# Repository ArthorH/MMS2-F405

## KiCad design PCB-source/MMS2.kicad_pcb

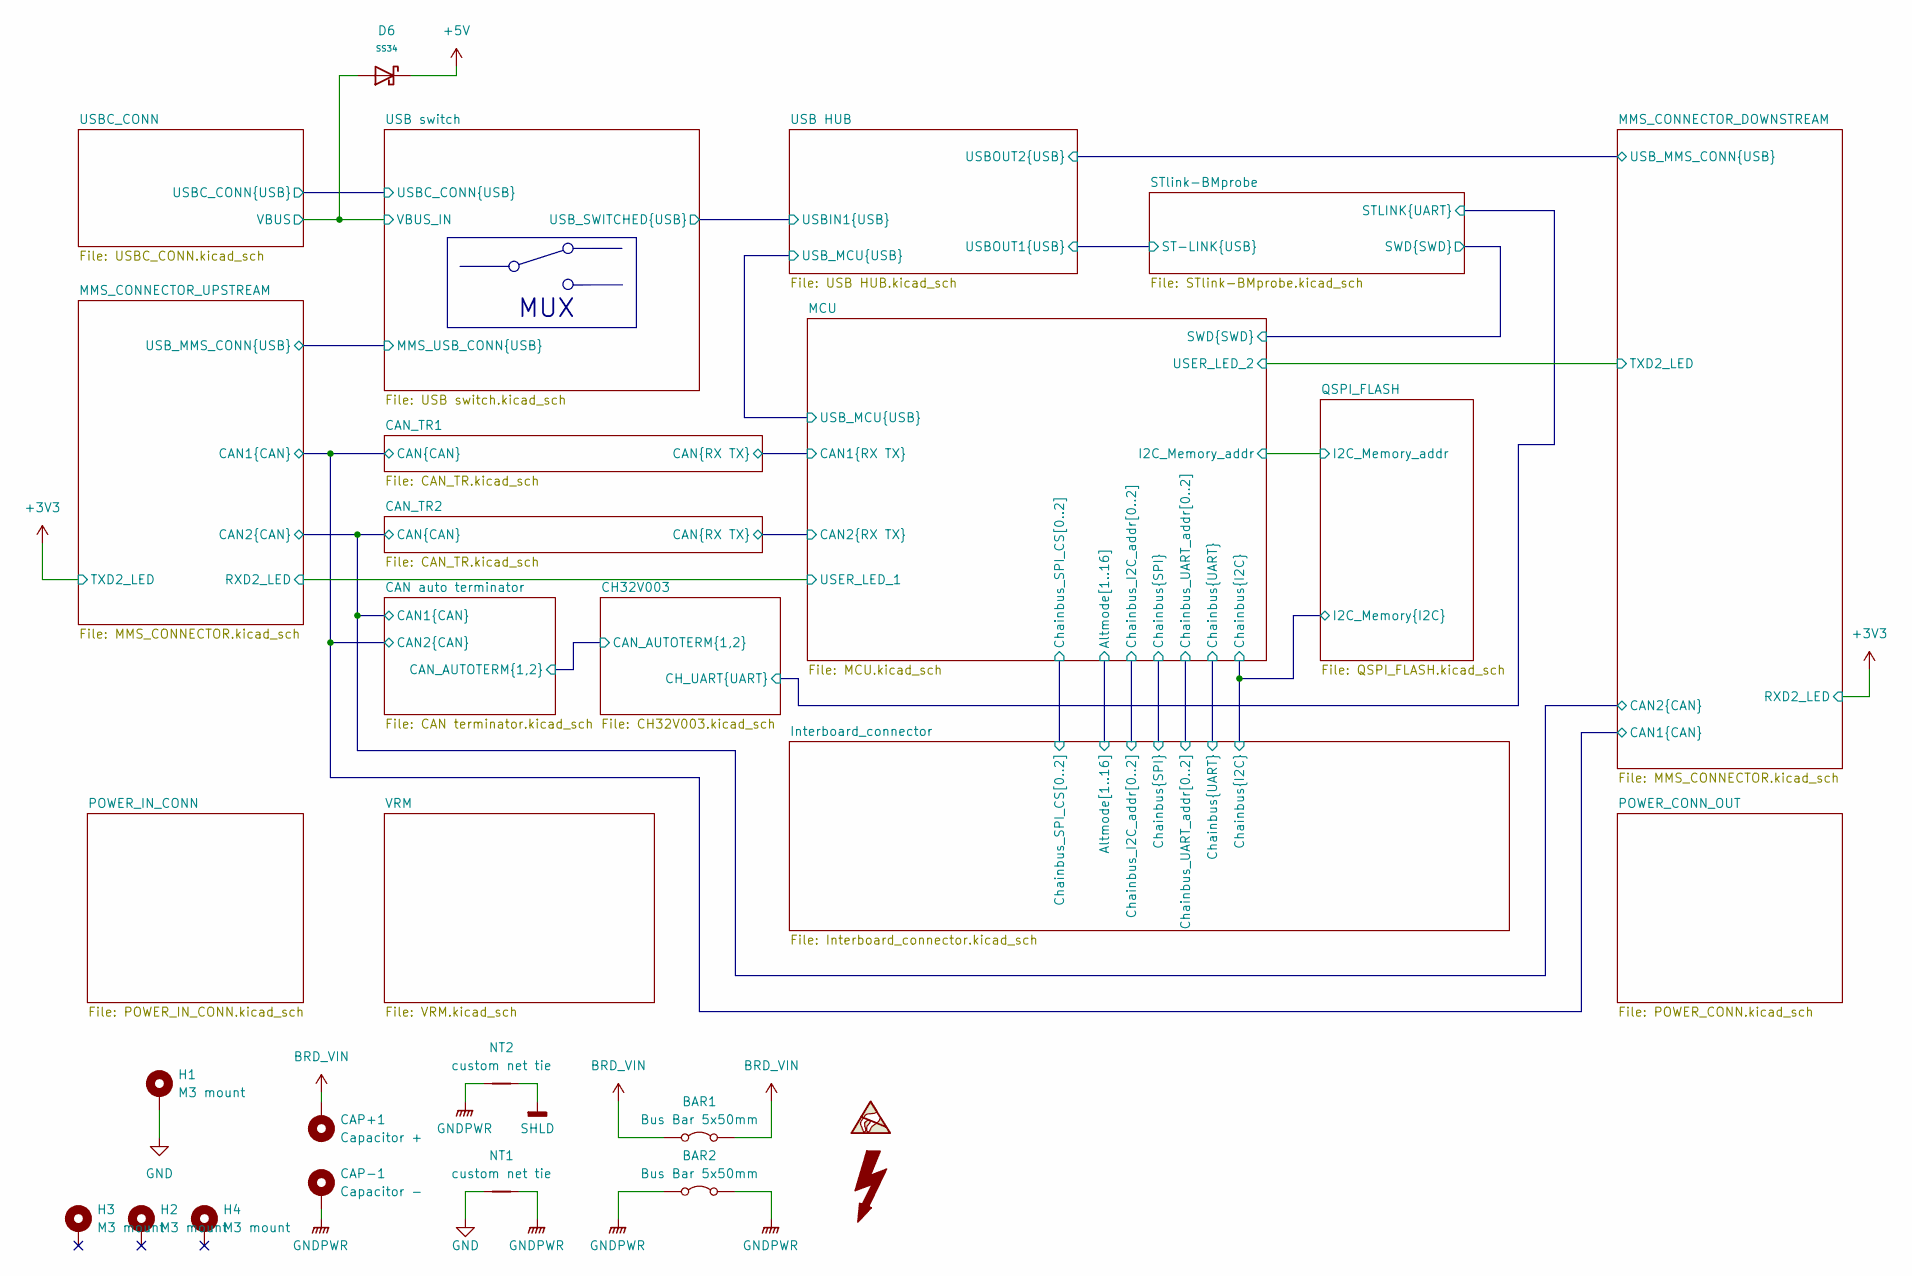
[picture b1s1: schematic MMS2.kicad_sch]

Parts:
BAR1: Bus Bar 5x50mm; BusBar-50mm-Red
BAR2: Bus Bar 5x50mm; BusBar-50mm-black
CAP+1: Capacitor +; TestPoint_THTPad_1.5x1.5mm_Drill0.7mm
CAP-1: Capacitor -; TestPoint_THTPad_1.5x1.5mm_Drill0.7mm
D6: SS34; D_SMA; Forward Voltage (Vf@If) 550mV@3A; Reverse Voltage (Vr) 40V; Part SS34; LCSC C8678
H1, H2: M3 mount; MountingHole_3.2mm_M3_DIN965_Pad
H3, H4: M3 mount; MountingHole_3.2mm_M3_DIN965_Pad; LCSC C49236535
NT1: custom net tie; Custom
NT2: custom net tie; SHLD

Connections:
+5V: D6.1; also elsewhere on the board
BRD_VIN: BAR1.1 (A), BAR1.2 (B), CAP+1.1; also elsewhere on the board
GND: H1.1, NT1.1; also elsewhere on the board
GNDPWR: BAR2.1 (A), BAR2.2 (B), CAP-1.1, NT1.2, NT2.1; also elsewhere on the board
SHLD: NT2.2
VBUS: D6.2; also elsewhere on the board

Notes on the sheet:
MUX

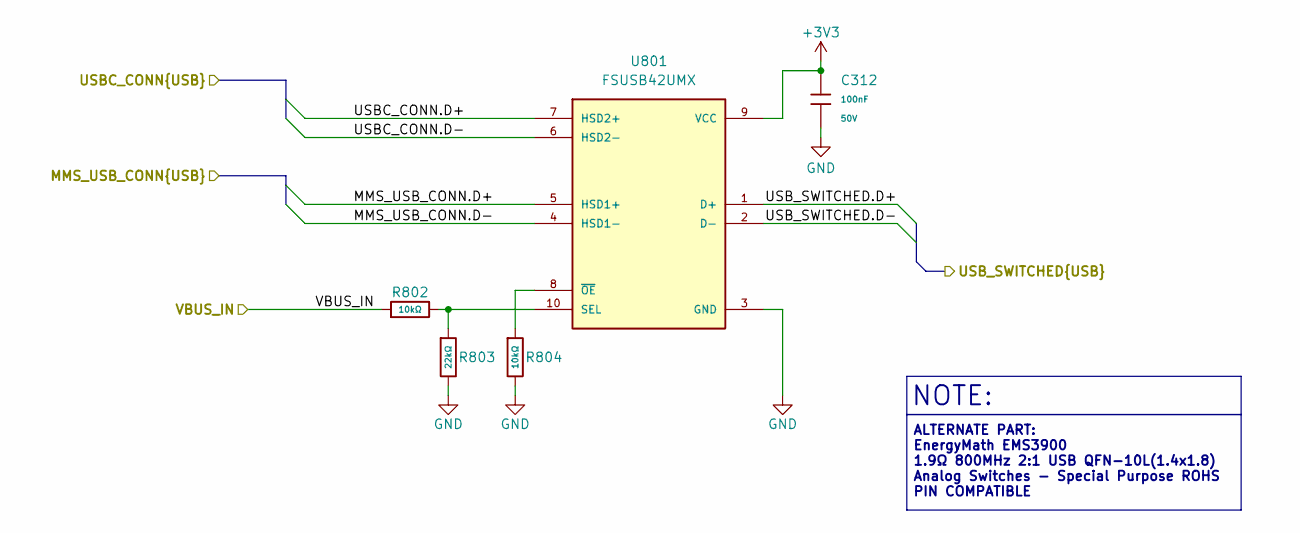
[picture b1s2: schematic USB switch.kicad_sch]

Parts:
C312: 100nF; C_0402; Voltage Rated 50V; Tolerance ±10%; Part CL05B104KB54PNC; LCSC C307331
R802, R804: 10kΩ; R_0402; Overload Voltage (Max) 50V; Tolerance ±1%; Part 0402WGF1002TCE; LCSC C25744
R803: 22kΩ; R_0402; Overload Voltage (Max) 50V; Tolerance ±1%; Part 0402WGF2202TCE; LCSC C25768
U801: FSUSB42UMX; UFQFN-10_1.4x1.8; PARTREV 1.25; LCSC C11145

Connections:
+3V3: C312.1, U801.9 (VCC); also elsewhere on the board
/MMS_CONNECTOR_UPSTREAM/USB_MMS_CONN.D+: U801.5 (HSD1+); also elsewhere on the board
/MMS_CONNECTOR_UPSTREAM/USB_MMS_CONN.D-: U801.4 (HSD1-); also elsewhere on the board
/USB HUB/USBIN1.D+: U801.1 (D+); also elsewhere on the board
/USB HUB/USBIN1.D-: U801.2 (D-); also elsewhere on the board
/USB switch/USBC_CONN.D+: U801.7 (HSD2+); also elsewhere on the board
/USB switch/USBC_CONN.D-: U801.6 (HSD2-); also elsewhere on the board
GND: C312.2, R803.2, R804.2, U801.3 (GND); also elsewhere on the board
unnamed: R802.2, R803.1, U801.10 (SEL)
unnamed: R804.1, U801.8 (~OE)
VBUS: R802.1; also elsewhere on the board

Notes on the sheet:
NOTE:
ALTERNATE PART: EnergyMath EMS3900 1.9Ω 800MHz 2:1 USB QFN-10L(1.4x1.8) Analog Switches - Special Purpose ROHS PIN COMPATIBLE

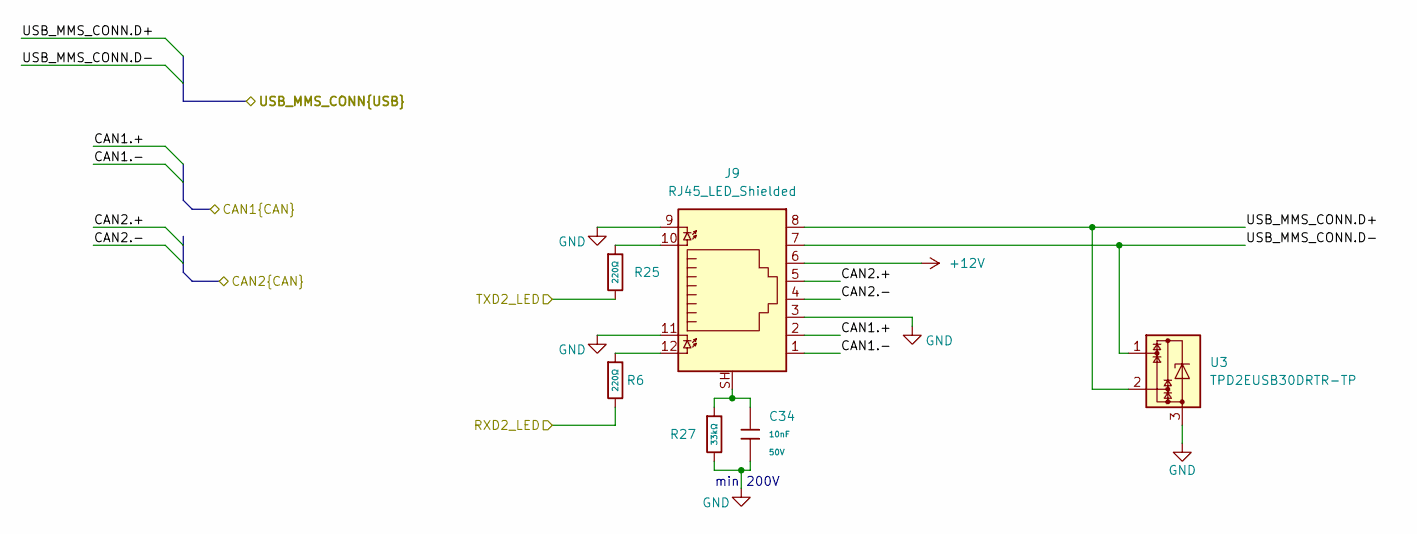
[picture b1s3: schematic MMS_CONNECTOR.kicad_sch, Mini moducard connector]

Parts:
C34: 10nF; C_0402; Voltage Rated 50V; Tolerance ±10%; Part CL05B103KB5NNNC; LCSC C15195
J9: RJ45_LED_Shielded; RJ45_Amphenol_RJHSE538X
R6, R25: 220Ω; R_0402; Overload Voltage (Max) 50V; Tolerance ±1%; Part 0402WGF2200TCE; LCSC C25091
R27: 33kΩ; R_0402; Overload Voltage (Max) 50V; Tolerance ±1%; Part 0402WGF3302TCE; LCSC C25779
U3: TPD2EUSB30DRTR-TP; SOT-723; LCSC C2844720

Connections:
+3V3: R6.2; also elsewhere on the board
+12V: J9.6; also elsewhere on the board
/CAN auto terminator/CAN1.+: J9.5; also elsewhere on the board
/CAN auto terminator/CAN1.-: J9.4; also elsewhere on the board
/CAN auto terminator/CAN2.+: J9.2; also elsewhere on the board
/CAN auto terminator/CAN2.-: J9.1; also elsewhere on the board
/MCU/USER_LED_2: R25.2; also elsewhere on the board
/MMS_CONNECTOR_DOWNSTREAM/USB_MMS_CONN.D+: J9.8, U3.2; also elsewhere on the board
/MMS_CONNECTOR_DOWNSTREAM/USB_MMS_CONN.D-: J9.7, U3.1; also elsewhere on the board
GND: C34.2, J9.3, J9.9, J9.11, R27.2, U3.3; also elsewhere on the board
unnamed: C34.1, J9.SH, R27.1
unnamed: J9.10, R25.1
unnamed: J9.12, R6.1

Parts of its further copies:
C45: 10nF; C_0402; Voltage Rated 50V; Tolerance ±10%; Part CL05B103KB5NNNC; LCSC C15195
J8: RJ45_LED_Shielded; RJ45_Amphenol_RJHSE538X
R26, R53: 220Ω; R_0402; Overload Voltage (Max) 50V; Tolerance ±1%; Part 0402WGF2200TCE; LCSC C25091
R51: 33kΩ; R_0402; Overload Voltage (Max) 50V; Tolerance ±1%; Part 0402WGF3302TCE; LCSC C25779
U4: TPD2EUSB30DRTR-TP; SOT-723; LCSC C2844720

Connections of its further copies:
+3V3: R26.2; also elsewhere on the board
+12V: J8.6; also elsewhere on the board
/CAN auto terminator/CAN1.+: J8.5; also elsewhere on the board
/CAN auto terminator/CAN1.-: J8.4; also elsewhere on the board
/CAN auto terminator/CAN2.+: J8.2; also elsewhere on the board
/CAN auto terminator/CAN2.-: J8.1; also elsewhere on the board
/MCU/USER_LED_1: R53.2; also elsewhere on the board
/MMS_CONNECTOR_UPSTREAM/USB_MMS_CONN.D+: J8.8, U4.2; also elsewhere on the board
/MMS_CONNECTOR_UPSTREAM/USB_MMS_CONN.D-: J8.7, U4.1; also elsewhere on the board
GND: C45.2, J8.3, J8.9, J8.11, R51.2, U4.3; also elsewhere on the board
unnamed: C45.1, J8.SH, R51.1
unnamed: J8.10, R26.1
unnamed: J8.12, R53.1

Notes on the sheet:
min 200V

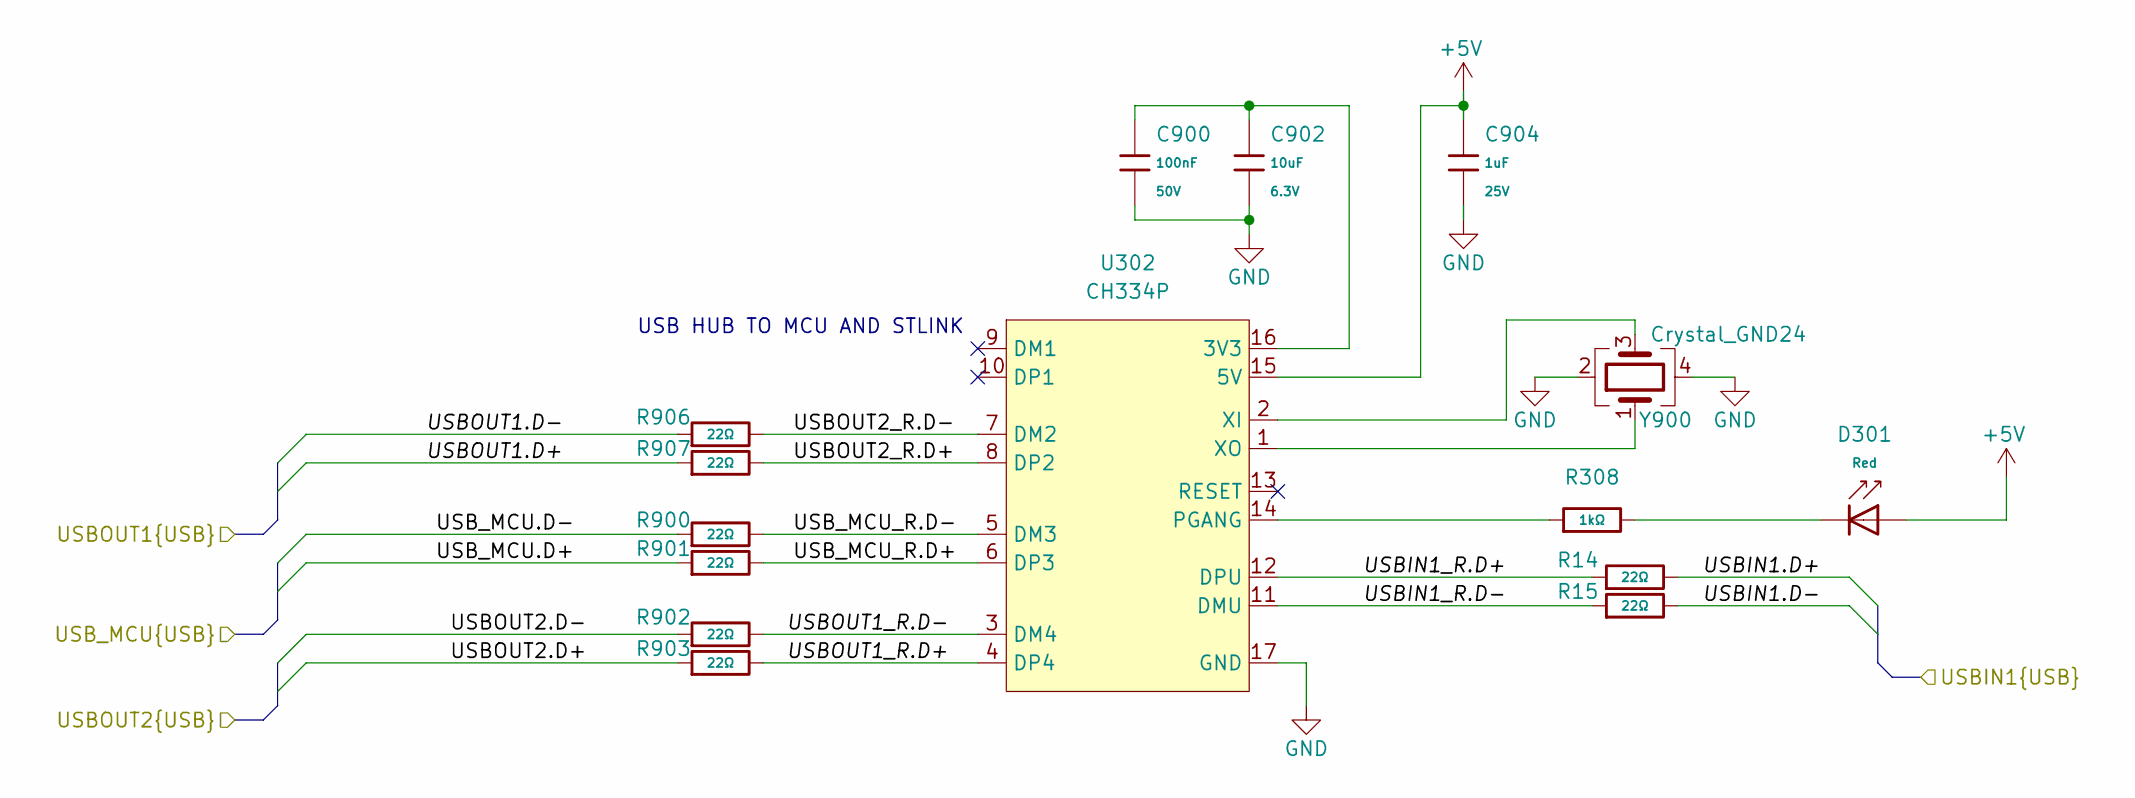
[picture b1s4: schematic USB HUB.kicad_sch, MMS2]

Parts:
C900: 100nF; C_0402; Voltage Rated 50V; Tolerance ±10%; Part CL05B104KB54PNC; LCSC C307331
C902: 10uF; C_0402; Voltage Rated 6.3V; Tolerance ±20%; Part CL05A106MQ5NUNC; LCSC C15525
C904: 1uF; C_0402; Voltage Rated 25V; Tolerance ±10%; Part CL05A105KA5NQNC; LCSC C52923
D301: Red; D_0603; Part KT-0603R; LCSC C2286
R14, R15, R900, R901, R902, R903, R906, R907: 22Ω; R_0402; Overload Voltage (Max) 50V; Tolerance ±1%; Part 0402WGF220JTCE; LCSC C25092
R308: 1kΩ; R_0402; Overload Voltage (Max) 50V; Tolerance ±1%; Part 0402WGF1001TCE; LCSC C11702
U302: CH334P; QFN-16-1EP_3x3mm_P0.5mm_EP1.7x1.7mm
Y900: Crystal_GND24; Crystal_SMD_3225-4Pin_3.2x2.5mm; LCSC C9002

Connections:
+5V: C904.1, D301.2, U302.15 (5V); also elsewhere on the board
/MCU/USB_MCU.D+: R901.1; also elsewhere on the board
/MCU/USB_MCU.D-: R900.1; also elsewhere on the board
/MMS_CONNECTOR_DOWNSTREAM/USB_MMS_CONN.D+: R903.1; also elsewhere on the board
/MMS_CONNECTOR_DOWNSTREAM/USB_MMS_CONN.D-: R902.1; also elsewhere on the board
/STlink-BMprobe/ST-LINK.D+: R907.1; also elsewhere on the board
/STlink-BMprobe/ST-LINK.D-: R906.1; also elsewhere on the board
/USB HUB/USBIN1.D+: R14.2; also elsewhere on the board
/USB HUB/USBIN1.D-: R15.2; also elsewhere on the board
/USB HUB/USBIN1_R.D+: R14.1, U302.12 (DPU)
/USB HUB/USBIN1_R.D-: R15.1, U302.11 (DMU)
/USB HUB/USBOUT1_R.D+: R903.2, U302.4 (DP4)
/USB HUB/USBOUT1_R.D-: R902.2, U302.3 (DM4)
/USB HUB/USBOUT2_R.D+: R907.2, U302.8 (DP2)
/USB HUB/USBOUT2_R.D-: R906.2, U302.7 (DM2)
/USB HUB/USB_MCU_R.D+: R901.2, U302.6 (DP3)
/USB HUB/USB_MCU_R.D-: R900.2, U302.5 (DM3)
GND: C900.2, C902.2, C904.2, U302.17 (GND), Y900.2, Y900.4; also elsewhere on the board
unnamed: D301.1, R308.2
unnamed: C900.1, C902.1, U302.16 (3V3)
unnamed: R308.1, U302.14 (PGANG)
unnamed: U302.2 (XI), Y900.3
unnamed: U302.1 (XO), Y900.1

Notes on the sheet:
USB HUB TO MCU AND STLINK

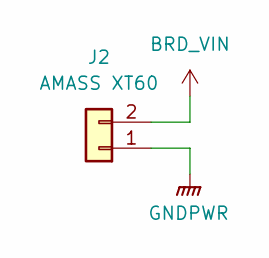
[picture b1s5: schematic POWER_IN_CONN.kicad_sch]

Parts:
J2: AMASS XT60; AMASS_XT60PW-M_1x02_P7.20mm_Horizontal; LCSC C98732

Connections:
BRD_VIN: J2.2; also elsewhere on the board
GNDPWR: J2.1; also elsewhere on the board

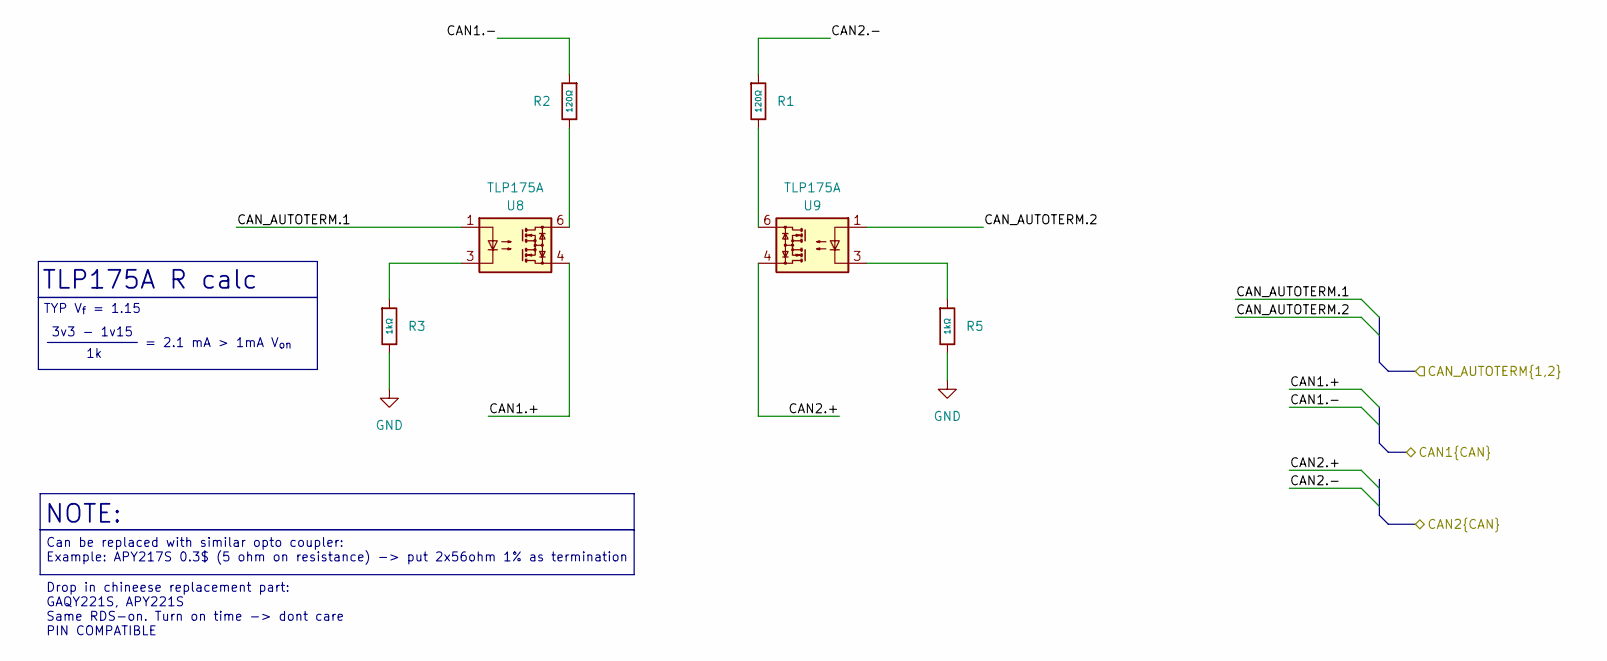
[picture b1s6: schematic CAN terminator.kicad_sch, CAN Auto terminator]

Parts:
R1, R2: 120Ω; R_0402; Overload Voltage (Max) 50V; Tolerance ±1%; Part 0402WGF1200TCE; LCSC C25079
R3, R5: 1kΩ; R_0402; Overload Voltage (Max) 50V; Tolerance ±1%; Part 0402WGF1001TCE; LCSC C11702
U8, U9: TLP175A; Toshiba_SOIC-4-6_4.4x3.6mm_P1.27mm; LCSC C141522

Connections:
/CAN auto terminator/CAN1.+: U8.4; also elsewhere on the board
/CAN auto terminator/CAN1.-: R2.1; also elsewhere on the board
/CAN auto terminator/CAN2.+: U9.4; also elsewhere on the board
/CAN auto terminator/CAN2.-: R1.1; also elsewhere on the board
/CAN auto terminator/CAN_AUTOTERM.1: U8.1; also elsewhere on the board
/CAN auto terminator/CAN_AUTOTERM.2: U9.1; also elsewhere on the board
GND: R3.2, R5.2; also elsewhere on the board
unnamed: R1.2, U9.6
unnamed: R2.2, U8.6
unnamed: R3.1, U8.3
unnamed: R5.1, U9.3

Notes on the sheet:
TYP V_{f} = 1.15
Can be replaced with similar opto coupler: Example: APY217S 0.3$ (5 ohm on resistance) -> put 2x56ohm 1% as termination
TLP175A R calc
3v3 - 1v15
Drop in chineese replacement part: GAQY221S, APY221S Same RDS-on. Turn on time -> dont care PIN COMPATIBLE
= 2.1 mA > 1mA V_{on}
NOTE:

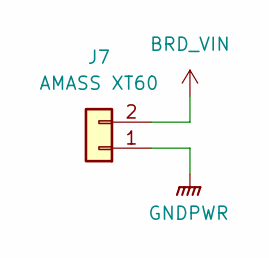
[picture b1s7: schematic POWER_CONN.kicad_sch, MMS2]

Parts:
J7: AMASS XT60; AMASS_XT60PW-F_1x02_P7.20mm_Horizontal; LCSC C428722

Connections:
BRD_VIN: J7.2; also elsewhere on the board
GNDPWR: J7.1; also elsewhere on the board

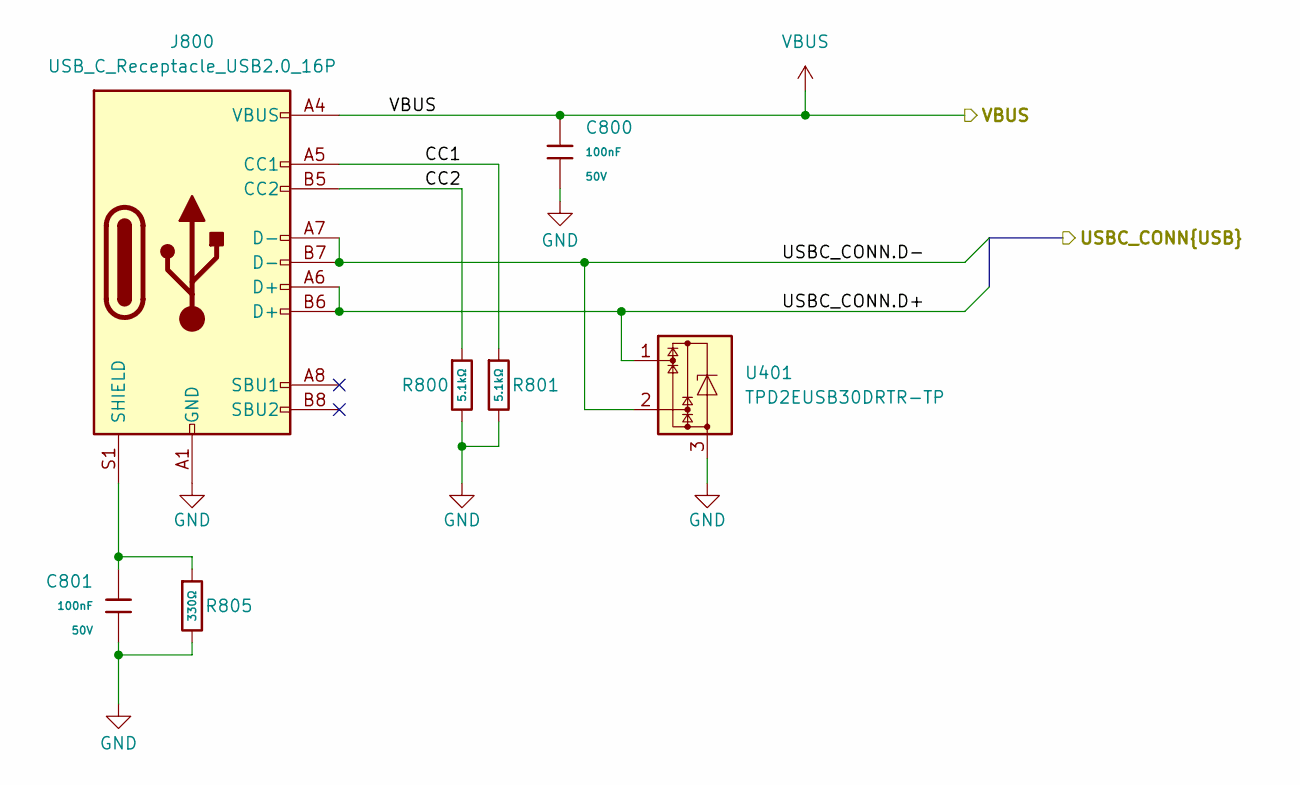
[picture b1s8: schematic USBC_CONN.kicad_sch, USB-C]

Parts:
C800, C801: 100nF; C_0402; Voltage Rated 50V; Tolerance ±10%; Part CL05B104KB54PNC; LCSC C307331
J800: USB_C_Receptacle_USB2.0_16P; USB_C_Receptacle_GCT_USB4105-xx-A_16P_TopMnt_Horizontal; LCSC C165948
R800, R801: 5.1kΩ; R_0402; Overload Voltage (Max) 50V; Tolerance ±1%; Part 0402WGF5101TCE; LCSC C25905
R805: 330Ω; R_0402; Overload Voltage (Max) 50V; Tolerance ±1%; Part 0402WGF3300TCE; LCSC C25104
U401: TPD2EUSB30DRTR-TP; SOT-723; LCSC C2844720

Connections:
/USB switch/USBC_CONN.D+: J800.A6 (D+), J800.B6 (D+), U401.1; also elsewhere on the board
/USB switch/USBC_CONN.D-: J800.A7 (D-), J800.B7 (D-), U401.2; also elsewhere on the board
/USBC_CONN/CC1: J800.A5 (CC1), R801.1
/USBC_CONN/CC2: J800.B5 (CC2), R800.1
GND: C800.2, C801.2, J800.A1 (GND), J800.A12 (GND), J800.B1 (GND), J800.B12 (GND), R800.2, R801.2, R805.2, U401.3; also elsewhere on the board
unnamed: C801.1, J800.S1 (SHIELD), R805.1
VBUS: C800.1, J800.A4 (VBUS), J800.A9 (VBUS), J800.B4 (VBUS), J800.B9 (VBUS); also elsewhere on the board

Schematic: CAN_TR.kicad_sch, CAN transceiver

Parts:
C500, C501: 100nF; C_0402; Voltage Rated 50V; Tolerance ±10%; Part CL05B104KB54PNC; LCSC C307331
R500: 10kΩ; R_0402; Overload Voltage (Max) 50V; Tolerance ±1%; Part 0402WGF1002TCE; LCSC C25744
U500: TJA1044GTK_3Z; HVSON-8-1EP_3x3mm_P0.65mm_EP1.6x2.4mm; Manufacturer_Part_Number TJA1044GTK/3Z; LCSC C5215851

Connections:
+3V3: C501.1, U500.5 (VIO); also elsewhere on the board
+5V: C500.2, U500.3 (VCC); also elsewhere on the board
/CAN auto terminator/CAN2.+: U500.7 (CANH); also elsewhere on the board
/CAN auto terminator/CAN2.-: U500.6 (CANL); also elsewhere on the board
/CAN_TR1/CAN.RX: U500.4 (RXD); also elsewhere on the board
/CAN_TR1/CAN.TX: U500.1 (TXD); also elsewhere on the board
GND: C500.1, C501.2, R500.2, U500.2 (GND), U500.9 (EP); also elsewhere on the board
unnamed: R500.1, U500.8 (STB)

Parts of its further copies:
C502, C503: 100nF; C_0402; Voltage Rated 50V; Tolerance ±10%; Part CL05B104KB54PNC; LCSC C307331
R501: 10kΩ; R_0402; Overload Voltage (Max) 50V; Tolerance ±1%; Part 0402WGF1002TCE; LCSC C25744
U501: TJA1044GTK_3Z; HVSON-8-1EP_3x3mm_P0.65mm_EP1.6x2.4mm; Manufacturer_Part_Number TJA1044GTK/3Z; LCSC C5215851

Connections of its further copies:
+3V3: C503.1, U501.5 (VIO); also elsewhere on the board
+5V: C502.2, U501.3 (VCC); also elsewhere on the board
/CAN auto terminator/CAN1.+: U501.7 (CANH); also elsewhere on the board
/CAN auto terminator/CAN1.-: U501.6 (CANL); also elsewhere on the board
/CAN_TR2/CAN.RX: U501.4 (RXD); also elsewhere on the board
/CAN_TR2/CAN.TX: U501.1 (TXD); also elsewhere on the board
GND: C502.1, C503.2, R501.2, U501.2 (GND), U501.9 (EP); also elsewhere on the board
unnamed: R501.1, U501.8 (STB)

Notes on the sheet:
CAN TRANSCEIVER

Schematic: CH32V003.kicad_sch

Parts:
C33: 100nF; C_0402; Voltage Rated 50V; Tolerance ±10%; Part CL05B104KB54PNC; LCSC C307331
D3, D4: Red; D_0603; Part KT-0603R; LCSC C2286
J5: Conn_01x03_Pin; PinHeader_1x03_P1.27mm_Vertical
R23, R24: 220Ω; R_0402; Overload Voltage (Max) 50V; Tolerance ±1%; Part 0402WGF2200TCE; LCSC C25091
U7: CH32V003FxUx; QFN-20-1EP_3x3mm_P0.4mm_EP1.65x1.65mm; LCSC C5299908

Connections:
+3V3: C33.1, U7.6 (VDD); also elsewhere on the board
/CAN auto terminator/CAN_AUTOTERM.1: U7.11 (PC4); also elsewhere on the board
/CAN auto terminator/CAN_AUTOTERM.2: U7.10 (PC3); also elsewhere on the board
/CH32V003/CH_UART.RX: U7.20 (PD6); also elsewhere on the board
/CH32V003/CH_UART.TX: U7.19 (PD5); also elsewhere on the board
/CH32V003/LED1: D4.2, U7.14 (PC7)
/CH32V003/LED2: D3.2, U7.16 (PD2)
/CH32V003/RST: J5.2, U7.1 (PD7)
/CH32V003/SWIO: J5.3, U7.15 (PD1)
GND: C33.2, J5.1, R23.2, R24.2, U7.4 (VSS), U7.21 (VSS); also elsewhere on the board
unnamed: D3.1, R23.1
unnamed: D4.1, R24.1

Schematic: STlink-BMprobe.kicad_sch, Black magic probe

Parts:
C700: 1uF; C_0402; Voltage Rated 25V; Tolerance ±10%; Part CL05A105KA5NQNC; LCSC C52923
C701, C702, C703, C704, C705, C706: 100nF; C_0402; Voltage Rated 50V; Tolerance ±10%; Part CL05B104KB54PNC; LCSC C307331
C707, C708: 33pF; C_0402; Voltage Rated 50V; Tolerance ±5%; Part 0402CG330J500NT; LCSC C1562
D700, D701: Red; D_0603; Part KT-0603R; LCSC C2286
J3: Programming header; PinHeader_1x06_P1.27mm_Vertical
Q700: MMST3904; SOT-23; Part MMST3904; LCSC C20526
R700, R702: 100kΩ; R_0402; Overload Voltage (Max) 50V; Tolerance ±1%; Part 0402WGF1003TCE; LCSC C25741
R701, R703, R705, R709: 10kΩ; R_0402; Overload Voltage (Max) 50V; Tolerance ±1%; Part 0402WGF1002TCE; LCSC C25744
R704, R708, R715, R716: 22Ω; R_0402; Overload Voltage (Max) 50V; Tolerance ±1%; Part 0402WGF220JTCE; LCSC C25092
R706: 10kΩ; R_0402; Overload Voltage (Max) 50V; Tolerance ±1%; Part 0402WGF1002TCE; LCSC C25744; not fitted
R707, R713: 220Ω; R_0402; Overload Voltage (Max) 50V; Tolerance ±1%; Part 0402WGF2200TCE; LCSC C25091
R710, R714: 100Ω; R_0402; Overload Voltage (Max) 50V; Tolerance ±1%; Part 0402WGF1000TCE; LCSC C25076
R711: 24.9kΩ; R_0402; Overload Voltage (Max) 50V; Tolerance ±1%; Part 0402WGF2402TCE; LCSC C25874
R712: 1.5kΩ; R_0402; Overload Voltage (Max) 50V; Tolerance ±1%; Part 0402WGF1501TCE; LCSC C25867
U700: STM32F103CBTx; LQFP-48_7x7mm_P0.5mm; LCSC C8304
Y700: Crystal_GND24; CRYSTAL-SMD_4P-L3.2-W2.5-BL; MPN 3225-8.00-20-10-10/4B; LCSC C7424755

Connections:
+3V3: C700.1, C701.1, C702.1, C703.1, C704.1, C705.1, J3.1, Q700.3 (C), R700.1, R701.1, R707.1, U700.1 (VBAT), U700.9 (VDDA), U700.24 (VDD), U700.36 (VDD), U700.48 (VDD); also elsewhere on the board
+5V: R709.1; also elsewhere on the board
/CH32V003/CH_UART.RX: U700.12 (PA2); also elsewhere on the board
/CH32V003/CH_UART.TX: U700.13 (PA3); also elsewhere on the board
/MCU/SWD.SWCLK: R704.2, R715.1; also elsewhere on the board
/MCU/SWD.SWDIO: R716.1; also elsewhere on the board
/MCU/SWD.~RST: R708.1; also elsewhere on the board
/STlink-BMprobe/CLK: J3.3, U700.37 (PA14)
/STlink-BMprobe/DIO: J3.2, U700.34 (PA13)
/STlink-BMprobe/LED: D700.1, D701.2, U700.30 (PA9)
/STlink-BMprobe/ST-LINK.D+: R712.2, U700.33 (PA12); also elsewhere on the board
/STlink-BMprobe/ST-LINK.D-: U700.32 (PA11); also elsewhere on the board
/STlink-BMprobe/STLINK-BOOT0: J3.6, R702.2, U700.44 (BOOT0)
/STlink-BMprobe/STLINK-OSC_IN: C707.1, U700.5 (PD0), Y700.1
/STlink-BMprobe/STLINK-OSC_OUT: C708.1, U700.6 (PD1), Y700.3
/STlink-BMprobe/STLINK-RST: C706.1, J3.4, R700.2, U700.7 (NRST)
/STlink-BMprobe/SWO: U700.31 (PA10)
/STlink-BMprobe/USB_RENUM: R710.2, U700.38 (PA15)
GND: C700.2, C701.2, C702.2, C703.2, C704.2, C705.2, C706.2, C707.2, C708.2, J3.5, R702.1, R703.2, R705.1, R706.1, R711.2, R713.2, U700.8 (VSSA), U700.23 (VSS), U700.35 (VSS), U700.47 (VSS), Y700.2, Y700.4; also elsewhere on the board
unnamed: D700.2, R707.2
unnamed: D701.1, R713.1
unnamed: Q700.1 (B), R709.2, R710.1, R711.1
unnamed: Q700.2 (E), R712.1
unnamed: R701.2, R703.1, U700.10 (PA0)
unnamed: R704.1, U700.15 (PA5)
unnamed: R708.2, U700.18 (PB0)
unnamed: R714.2, U700.25 (PB12)
unnamed: R715.2, U700.26 (PB13)
unnamed: R714.1, R716.2, U700.27 (PB14)
unnamed: R705.2, U700.2 (PC13)
unnamed: R706.2, U700.3 (PC14)

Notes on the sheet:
ACTIVITY LED
NOTICE:
Alternative GD32F103CB
FORCE RENUMERATION OF USB DEVICES
for providing amazing reverse engeenering of ST-link
Monitor voltage rail 3V3 instead of target MCU voltage
UART FLIP HERE
https://github.com/lbthomsen/st-link/tree/master
SWD
NOTE:
MANDATORY CB VERSION
CAUTION:
Credit to:
https://stm32world.com/wiki/DIY_STM32_Programmer_(ST-Link/V2-1)
ALTERNATE PART: GigaDevice Semicon Beijing GD32F103CBT6 PIN AND FW COMPATIBLE WAZZUP BEIJING
Populate with STM32F103C8, STM32F103CB
Should be 1k5, but we try 1k2 because it is in basic parts
Do weryfikackji moducard nav module 2
C707=C708 = (CL - 4pF) * 2

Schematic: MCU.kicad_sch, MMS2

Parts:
C26, C29: 2.2uF; C_0402; Voltage Rated 6.3V; Tolerance ±20%; Part CL05A225MQ5NSNC; LCSC C12530
C30, C31: 22pF; C_0402; Voltage Rated 50V; Tolerance ±5%; Part 0402CG220J500NT; LCSC C1555
C313, C314: 18pF; C_0402; Voltage Rated 50V; Tolerance ±5%; Part 0402CG180J500NT; LCSC C1549
C400, C403, C423, C425: 10uF; C_0402; Voltage Rated 6.3V; Tolerance ±20%; Part CL05A106MQ5NUNC; LCSC C15525
C401, C402, C404, C415, C416, C422, C424, C426: 100nF; C_0402; Voltage Rated 50V; Tolerance ±10%; Part CL05B104KB54PNC; LCSC C307331
C410: 4.7uF; C_0402; Voltage Rated 10V; Tolerance ±20%; Part CL05A475MP5NRNC; LCSC C23733; not fitted
FB401: FB_0603; Current Rating 200mA; Tolerance ±25%; Part GZ1608D601TF; LCSC C1002
R401: 1kΩ; R_0402; Overload Voltage (Max) 50V; Tolerance ±1%; Part 0402WGF1001TCE; LCSC C11702; not fitted
R402, R403, R405: 10kΩ; R_0402; Overload Voltage (Max) 50V; Tolerance ±1%; Part 0402WGF1002TCE; LCSC C25744
R404, R406: 100Ω; R_0402; Overload Voltage (Max) 50V; Tolerance ±1%; Part 0402WGF1000TCE; LCSC C25076
SW1: BOOT; SW_Tactile_SPST_NO_Straight_CK_PTS636Sx25SMTRLFS; MPN TSB008A2530A; LCSC C22375371
SW2: RESET; SW_Tactile_SPST_NO_Straight_CK_PTS636Sx25SMTRLFS; MPN TSB008A2530A; LCSC C22375371
U1: STM32F405RGTx; LQFP-64_10x10mm_P0.5mm; LCSC C15742
X1: X32258MOB4SI; OSC-SMD_4P-L3.2-W2.5-BL; Frequency Tolerance ±10ppm; Part X322525MOB4SI; LCSC C2682775
X2: Q13FC1350000400; FC-135R_L3.2-W1.5; Frequency Tolerance ±20ppm; Part Q13FC13500004; LCSC C97606

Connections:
+3V3: C400.1, C401.1, C402.1, C403.1, C404.1, C422.1, C425.1, C426.1, FB401.2, R403.1, R405.1, U1.1 (VBAT), U1.19 (VDD), U1.32 (VDD), U1.48 (VDD), U1.64 (VDD); also elsewhere on the board
/CAN_TR1/CAN.RX: U1.62 (PB9); also elsewhere on the board
/CAN_TR1/CAN.TX: U1.61 (PB8); also elsewhere on the board
/CAN_TR2/CAN.RX: U1.33 (PB12); also elsewhere on the board
/CAN_TR2/CAN.TX: U1.58 (PB6); also elsewhere on the board
/Interboard_connector/Altmode1: U1.41 (PA8); also elsewhere on the board
/Interboard_connector/Altmode2: U1.42 (PA9); also elsewhere on the board
/Interboard_connector/Altmode3: U1.43 (PA10); also elsewhere on the board
/Interboard_connector/Altmode4: U1.34 (PB13); also elsewhere on the board
/Interboard_connector/Altmode5: U1.35 (PB14); also elsewhere on the board
/Interboard_connector/Altmode6: U1.36 (PB15); also elsewhere on the board
/Interboard_connector/Altmode7: U1.14 (PA0); also elsewhere on the board
/Interboard_connector/Altmode8: U1.15 (PA1); also elsewhere on the board
/Interboard_connector/Altmode9: U1.16 (PA2); also elsewhere on the board
/Interboard_connector/Altmode10: U1.17 (PA3); also elsewhere on the board
/Interboard_connector/Altmode11: U1.59 (PB7); also elsewhere on the board
/Interboard_connector/Altmode12: U1.8 (PC0); also elsewhere on the board
/Interboard_connector/Altmode13: U1.9 (PC1); also elsewhere on the board
/Interboard_connector/Altmode14: U1.10 (PC2); also elsewhere on the board
/Interboard_connector/Altmode15: U1.11 (PC3); also elsewhere on the board
/Interboard_connector/Altmode16: U1.24 (PC4); also elsewhere on the board
/Interboard_connector/Chainbus.MISO: U1.56 (PB4); also elsewhere on the board
/Interboard_connector/Chainbus.MOSI: U1.53 (PC12); also elsewhere on the board
/Interboard_connector/Chainbus.RX: U1.52 (PC11); also elsewhere on the board
/Interboard_connector/Chainbus.SCK: U1.55 (PB3); also elsewhere on the board
/Interboard_connector/Chainbus.SCL: U1.29 (PB10); also elsewhere on the board
/Interboard_connector/Chainbus.SDA: U1.30 (PB11); also elsewhere on the board
/Interboard_connector/Chainbus.TX: U1.51 (PC10); also elsewhere on the board
/Interboard_connector/Chainbus_I2C_addr0: U1.50 (PA15); also elsewhere on the board
/Interboard_connector/Chainbus_I2C_addr1: U1.57 (PB5); also elsewhere on the board
/Interboard_connector/Chainbus_I2C_addr2: U1.40 (PC9); also elsewhere on the board
/Interboard_connector/Chainbus_SPI_CS0: U1.37 (PC6); also elsewhere on the board
/Interboard_connector/Chainbus_SPI_CS1: U1.38 (PC7); also elsewhere on the board
/Interboard_connector/Chainbus_SPI_CS2: U1.39 (PC8); also elsewhere on the board
/Interboard_connector/Chainbus_UART_addr0: U1.22 (PA6); also elsewhere on the board
/Interboard_connector/Chainbus_UART_addr1: U1.23 (PA7); also elsewhere on the board
/Interboard_connector/Chainbus_UART_addr2: U1.21 (PA5); also elsewhere on the board
/MCU/BOOT0: C410.1, R401.2, R402.1, U1.60 (BOOT0)
/MCU/BOOT_EN: R401.1
/MCU/I2C_Memory_addr: U1.25 (PC5); also elsewhere on the board
/MCU/NRST: C415.1, R403.2, R404.1, U1.7 (NRST)
/MCU/OSC32_IN: C314.1, U1.3 (PC14), X2.2
/MCU/OSC32_OUT: C313.1, U1.4 (PC15), X2.1
/MCU/OSC_HSI_IN: C31.1, U1.5 (PH0), X1.3 (OSC)
/MCU/OSC_HSI_OUT: C30.1, U1.6 (PH1), X1.1 (OSC)
/MCU/SWD.SWCLK: U1.49 (PA14); also elsewhere on the board
/MCU/SWD.SWDIO: U1.46 (PA13); also elsewhere on the board
/MCU/SWD.~RST: R404.2, SW2.1; also elsewhere on the board
/MCU/USB_MCU.D+: U1.45 (PA12); also elsewhere on the board
/MCU/USB_MCU.D-: U1.44 (PA11); also elsewhere on the board
/MCU/USER_LED_1: U1.27 (PB1); also elsewhere on the board
/MCU/USER_LED_2: U1.26 (PB0); also elsewhere on the board
/MCU/USR_BTN: C416.1, R405.2, R406.1
/MCU/USR_BUTTON: R406.2, SW1.1, U1.54 (PD2)
/MCU/VDDA: C423.1, C424.1, FB401.1, U1.13 (VDDA)
GND: C26.2, C29.2, C30.2, C31.2, C313.2, C314.2, C400.2, C401.2, C402.2, C403.2, C404.2, C410.2, C415.2, C416.2, C422.2, C423.2, C424.2, C425.2, C426.2, R402.2, SW1.2, SW2.2, U1.12 (VSSA), U1.18 (VSS), U1.63 (VSS), X1.2 (GND), X1.4 (GND); also elsewhere on the board
unnamed: C29.1, U1.31 (VCAP_1)
unnamed: C26.1, U1.47 (VCAP_2)

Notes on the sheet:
UART FLIP HERE
NOTICE:
SWD
NOTE:
CHAINBUS UART
NOTE: PLACE CAPACTITOR AT PWR PIN
I2C MEME
Target I_{LED} = 5mA
CHAINBUS SPI
Boot EN can be pulled up with BOOT_EN pin C412 will retain voltage on boot0 pin during MCU reboot routine
ALTMODE HEADER
AVDD
AUTO BOOT SEL
POWER INDICATOR AND USER LEDs
USB
CAN
ALTERNATE PART: APM32F405RGT6 - C5290473 CKS32F405RGT6 - C5185730 GD32F405RGT6 - C99031
RESET BUTTON
CHAINBUS I2C
USER BUTTON
BULK
REV A. NC
CRYSTAL RESONATORS

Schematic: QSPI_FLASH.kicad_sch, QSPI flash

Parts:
C32: 100nF; C_0402; Voltage Rated 50V; Tolerance ±10%; Part CL05B104KB54PNC; LCSC C307331
R16, R17, R18, R22: 10kΩ; R_0402; Overload Voltage (Max) 50V; Tolerance ±1%; Part 0402WGF1002TCE; LCSC C25744
R19, R20, R21: 10kΩ; R_0402; Overload Voltage (Max) 50V; Tolerance ±1%; Part 0402WGF1002TCE; LCSC C25744; not fitted
U6: AT24C256C; SOIC-8_L4.9-W3.9-P1.27-LS6.0-BL; Supply Voltage 1.7V~5.5V; Part AT24C256C-SSHL-T; LCSC C6482

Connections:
+3V3: C32.1, R19.1, R20.1, R21.1, U6.8 (VCC); also elsewhere on the board
/Interboard_connector/Chainbus.SCL: U6.6 (SCL); also elsewhere on the board
/Interboard_connector/Chainbus.SDA: U6.5 (SDA); also elsewhere on the board
/MCU/I2C_Memory_addr: R21.2, R22.1, U6.1 (A0); also elsewhere on the board
/QSPI_FLASH/A1: R18.1, R20.2, U6.2 (A1)
/QSPI_FLASH/A2: R17.1, R19.2, U6.3 (A2)
GND: C32.2, R16.2, R17.2, R18.2, R22.2, U6.4 (GND); also elsewhere on the board
unnamed: R16.1, U6.7 (WP)

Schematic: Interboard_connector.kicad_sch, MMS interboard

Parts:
J1: 86093488324755V1LF; AMPHENOL_86093488324755V1LF; PARTREV C; LCSC C5173373
J4: Conn_01x16_Socket; PinSocket_1x16_P2.54mm_Vertical

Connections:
+3V3: J1.A16, J4.16; also elsewhere on the board
+5V: J1.A15, J4.15; also elsewhere on the board
/Interboard_connector/Altmode1: J1.C1; also elsewhere on the board
/Interboard_connector/Altmode2: J1.C2; also elsewhere on the board
/Interboard_connector/Altmode3: J1.C3; also elsewhere on the board
/Interboard_connector/Altmode4: J1.C4; also elsewhere on the board
/Interboard_connector/Altmode5: J1.C5; also elsewhere on the board
/Interboard_connector/Altmode6: J1.C6; also elsewhere on the board
/Interboard_connector/Altmode7: J1.C12; also elsewhere on the board
/Interboard_connector/Altmode8: J1.C13; also elsewhere on the board
/Interboard_connector/Altmode9: J1.C14; also elsewhere on the board
/Interboard_connector/Altmode10: J1.C15; also elsewhere on the board
/Interboard_connector/Altmode11: J1.C7; also elsewhere on the board
/Interboard_connector/Altmode12: J1.C8; also elsewhere on the board
/Interboard_connector/Altmode13: J1.C9; also elsewhere on the board
/Interboard_connector/Altmode14: J1.C10; also elsewhere on the board
/Interboard_connector/Altmode15: J1.C11; also elsewhere on the board
/Interboard_connector/Altmode16: J1.C16; also elsewhere on the board
/Interboard_connector/Chainbus.MISO: J1.B6; also elsewhere on the board
/Interboard_connector/Chainbus.MOSI: J1.B7; also elsewhere on the board
/Interboard_connector/Chainbus.RX: J1.B1; also elsewhere on the board
/Interboard_connector/Chainbus.SCK: J1.B8; also elsewhere on the board
/Interboard_connector/Chainbus.SCL: J1.B15; also elsewhere on the board
/Interboard_connector/Chainbus.SDA: J1.B16; also elsewhere on the board
/Interboard_connector/Chainbus.TX: J1.B2; also elsewhere on the board
/Interboard_connector/Chainbus_I2C_addr0: J1.B9; also elsewhere on the board
/Interboard_connector/Chainbus_I2C_addr1: J1.B10; also elsewhere on the board
/Interboard_connector/Chainbus_I2C_addr2: J1.B11; also elsewhere on the board
/Interboard_connector/Chainbus_SPI_CS0: J1.B12; also elsewhere on the board
/Interboard_connector/Chainbus_SPI_CS1: J1.B13; also elsewhere on the board
/Interboard_connector/Chainbus_SPI_CS2: J1.B14; also elsewhere on the board
/Interboard_connector/Chainbus_UART_addr0: J1.B3; also elsewhere on the board
/Interboard_connector/Chainbus_UART_addr1: J1.B4; also elsewhere on the board
/Interboard_connector/Chainbus_UART_addr2: J1.B5; also elsewhere on the board
BRD_VIN: J1.A10, J1.A11, J1.A12, J1.A13, J4.10, J4.11, J4.12, J4.13; also elsewhere on the board
GND: J1.A6, J1.A7, J1.A8, J1.A9, J1.A14, J4.6, J4.7, J4.8, J4.9, J4.14; also elsewhere on the board

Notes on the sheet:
ALTMODE HEADER
